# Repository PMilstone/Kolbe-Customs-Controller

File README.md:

# Kolbe Customs Controller

This project is a remix of the Flatbox rev5 by jfedor2 here: https://github.com/jfedor2/flatbox/tree/master/hardware-rev5. The changes made are the following:

- Shadow lines to make a cleaner seam
- Use of M3 heat inserts
- Compatibility with Choc v2 switches

This project requires the following:

- [3D printed](3d-models) top and bottom case, 11 24mm buttons, and 1 or 2 30mm buttons
- The [PCB](pcb), with or without the USB passthrough assembely
- [RP2040-Zero](https://www.waveshare.com/rp2040-zero.htm)
- 6x [6x6x5mm tactile switches](https://www.amazon.com/gp/product/B01CGMP9GY/ref=ppx_yo_dt_b_search_asin_title?ie=UTF8&psc=1) (these come on the PCB if you buy it preassembled via jlpcb)
- Optional [USB port](https://www.mouser.com/ProductDetail/640-USB1046GF0190LBA) if using USB passthrough for Xbox S|X or PS5
- 12 or 13 [Kailh low profile (choc v2) switches](https://mechanicalkeyboards.com/shop/index.php?l=product_detail&p=6341) of your choice
- 12 or 13 [Kailh low profile hotswap sockets](https://mechanicalkeyboards.com/shop/index.php?l=product_detail&p=6995)
- 7x [M3 3.8mm heat set inserts](https://www.mcmaster.com/94180A331)
- 7x [M3 8mm Screws](https://www.mcmaster.com/91294A128) and wrench
- \(Optional)Right angle USB-C cable

Included in the 3D Models folder, there are 4 case tops. You will choose the coresponding top for if you want 2 thumb buttons, USB passthrough, or both. All options use the same bottom case.

I print my cases and buttons 0.3mm layer height with a 0.6mm nozzle.

To flash the firmware, connect the board to a computer with a USB cable, then press the RESET button while holding the BOOT button on the RP2040-Zero. A drive named "RPI-RP2" should appear. Copy the UF2 file you downloaded to that drive.

PCB design licensed under [CC BY-SA 4.0](https://creativecommons.org/licenses/by-sa/4.0/).

PCB design uses the following:

- [remix of jfedor2's flatbox rev5](https://github.com/jfedor2/flatbox/tree/master/hardware-rev5)
- [keyswitches.pretty](https://github.com/daprice/keyswitches.pretty) by [daprice](https://github.com/daprice) ([CC BY-SA 4.0](https://creativecommons.org/licenses/by-sa/4.0/))
- RP2040-Zero STEP file downloaded from [Waveshare wiki](https://www.waveshare.com/wiki/RP2040-Zero)

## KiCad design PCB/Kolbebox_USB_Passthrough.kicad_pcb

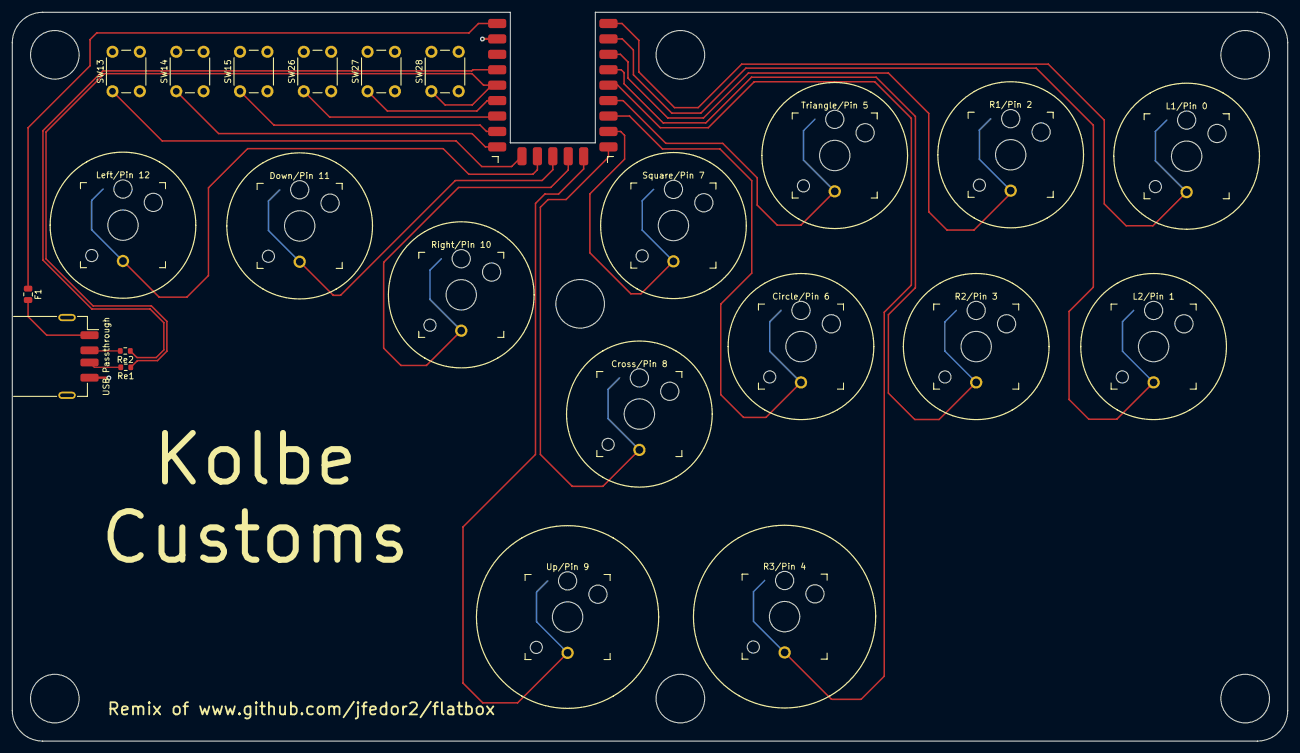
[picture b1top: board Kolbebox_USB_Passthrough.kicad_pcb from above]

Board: 2 copper layers, 210.0 x 120.0 mm, 31 parts (0 on the bottom side), 22 nets.

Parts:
A1: RP2040-Zero
Circle/Pin 6: SW_Push; Kailh_socket_PG1350_optional
Cross/Pin 8: SW_Push; Kailh_socket_PG1350_optional
Down/Pin 11: SW_Push; Kailh_socket_PG1350_optional
F1: Fuse; Fuse_0805_2012Metric
H1, H2, H3, H4, H5, H6, H7: MountingHole; MountingHole_6.4mm_M6
L1/Pin 0, L2/Pin 1: SW_Push; Kailh_socket_PG1350_optional
Left/Pin 12: SW_Push; Kailh_socket_PG1350_optional
R1/Pin 2, R2/Pin 3, R3/Pin 4: SW_Push; Kailh_socket_PG1350_optional
Re1: Resistor 1; R_0603_1608Metric
Re2: Resistor 2; R_0603_1608Metric
Right/Pin 10: SW_Push; Kailh_socket_PG1350_optional
SW13, SW14, SW15, SW26, SW27, SW28: SW_Push; SW_PUSH_6mm_H5mm
Square/Pin 7: SW_Push; Kailh_socket_PG1350_optional
Triangle/Pin 5: SW_Push; Kailh_socket_PG1350_optional
USB Passthrough: USB 2.0; USB_A_Receptacle_GCT_USB1046
Up/Pin 9: SW_Push; Kailh_socket_PG1350_optional

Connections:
5V: A1.32 (5V), F1.1, F1.2, USB Passthrough.1
CIRCLE: A1.6 (GPIO6), Circle/Pin 6.1
CROSS: A1.8 (GPIO8), Cross/Pin 8.1
D+: A1.28 (GPIO28), Re1.1, Re1.2, SW28.1, USB Passthrough.3
D-: A1.29 (GPIO29), Re2.1, Re2.2, USB Passthrough.2
DOWN: A1.11 (GPIO11), Down/Pin 11.1
GND: A1.31 (GND), Circle/Pin 6.2, Cross/Pin 8.2, Down/Pin 11.2, L1/Pin 0.2, L2/Pin 1.2, Left/Pin 12.2, R1/Pin 2.2, R2/Pin 3.2, R3/Pin 4.2, Right/Pin 10.2, SW13.2, SW14.2, SW15.2, SW26.2, SW27.2, SW28.2, Square/Pin 7.2, Triangle/Pin 5.2, USB Passthrough.4, Up/Pin 9.2
L1: A1.0 (GPIO0), L1/Pin 0.1
L2: A1.1 (GPIO1), L2/Pin 1.1
LEFT: A1.12 (GPIO12), Left/Pin 12.1
OPT1: A1.13 (GPIO13), SW13.1
OPT2: A1.14 (GPIO14), SW14.1
OPT3: A1.15 (GPIO15), SW15.1
OPT4: A1.26 (GPIO26), SW26.1
OPT5: A1.27 (GPIO27), SW27.1
R1: A1.2 (GPIO2), R1/Pin 2.1
R2: A1.3 (GPIO3), R2/Pin 3.1
RIGHT: A1.10 (GPIO10), Right/Pin 10.1
SQUARE: A1.7 (GPIO7), Square/Pin 7.1
TOUCH: A1.4 (GPIO4), R3/Pin 4.1
TRIANGLE: A1.5 (GPIO5), Triangle/Pin 5.1
UP: A1.9 (GPIO9), Up/Pin 9.1

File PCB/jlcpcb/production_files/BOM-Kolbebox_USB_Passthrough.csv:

Comment,Designator,Footprint,LCSC
SW_Push,SW26,SW_PUSH_6mm_H5mm,
SW_Push,SW14,SW_PUSH_6mm_H5mm,
SW_Push,SW27,SW_PUSH_6mm_H5mm,
SW_Push,SW13,SW_PUSH_6mm_H5mm,
SW_Push,SW15,SW_PUSH_6mm_H5mm,
SW_Push,SW28,SW_PUSH_6mm_H5mm,
RP2040-Zero,A1,RP2040-Zero,
Fuse,F1,Fuse_0805_2012Metric,
Resistor 2,Re2,R_0603_1608Metric,
Resistor 1,Re1,R_0603_1608Metric,

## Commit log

2024-03-05 Adding Pictures, Models, and PCB
    Adding Pictures, Models, and PCB
